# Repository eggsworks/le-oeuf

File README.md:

## Le Oeuf

An ultra-low profile (Kailh PG1425 "X Switch") keyboard inspired by Le Chiffre.

## Build guide (wired)

### BOM

- 36x 1N4148 diodes, SOD-123
- 36x Kailh PG1425 + caps
- 1x 74HC595D shift register, SOP-16
- 1x Seeed Studio XIAO RP2040

### Assembly

1. Solder all surface-mount components on the front of the board (diodes, shift register, XIAO)
2. Solder switches
3. Flash firmware, install caps, and enjoy :D

## Build guide (wireless)

Coming soon :D

## Accessories

- **["Oeuf Poché"](cases/oeuf-poche)** - A 3d-printable minimal case. Mounts with four self-tapping M2x4mm screws.
- **["SK-1425"](cases/SK-1425)** - A two-part case by [seirin-blu](https://github.com/seirin-blu).

## Firmware

ZMK firmware available from [eggsworks/zmk-config](https://github.com/eggsworks/zmk-config/)

## Production files

Gerbers, BOM, and centroid files have been added under [le-oeuf/production/](le-oeuf/production/). These Gerbers are optimized for production by PCBWay and may not necessarily be accepted by other manufacturers. The BOM and centroid file include only the diodes and the shift register, leaving the switches and MCU to be hand-soldered.

## License

This design is available under the terms of the [CERN-OHL-S](LICENSE).

## Acknowledgements

- MCU footprint derived from [ebastler/marbastlib](https://github.com/ebastler/marbastlib/)
- Switch footprint derived from [kicad-footprint-kailh-pg1425-x-switch](https://github.com/shikamiya/kicad-footprint-kailh-pg1425-x-switch)
- Layout derived from ergogen source supplied for [sporkus/le_capybara_keyboard](https://github.com/sporkus/le_capybara_keyboard)
- PCB art kindly provided by transthropology

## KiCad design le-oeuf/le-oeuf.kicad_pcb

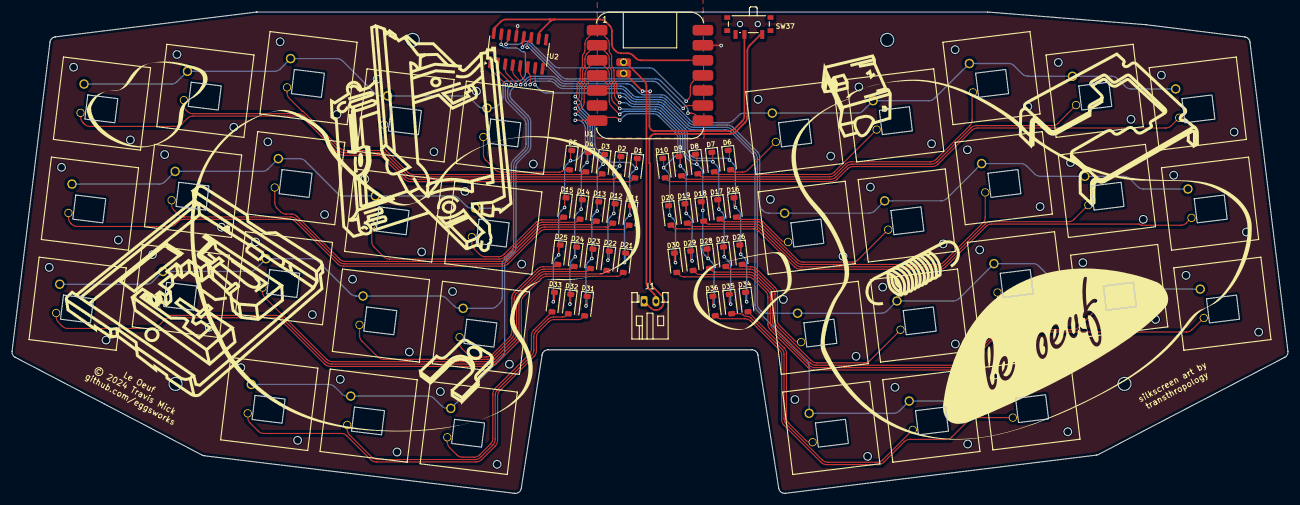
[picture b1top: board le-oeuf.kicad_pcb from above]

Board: 2 copper layers, 215.1 x 81.1 mm, 76 parts (0 on the bottom side), 57 nets.

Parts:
D1, D2, D3, D4, D5, D6, D7, D8, D9, D10, D11, D12, D13, D14, D15, D16, D17, D18, D19, D20, D21, D22, D23, D24, D25, D26, D27, D28, D29, D30, D31, D32, D33, D34, D35, D36: 1N4148W; D_SOD-123
J1: S2B-PH-K-S; JST_PH_S2B-PH-K_1x02_P2.00mm_Horizontal
SW1, SW2, SW3, SW4, SW5, SW6, SW7, SW8, SW9, SW10, SW11, SW12, SW13, SW14, SW15, SW16, SW17, SW18, SW19, SW20, SW21, SW22, SW23, SW24, SW25, SW26, SW27, SW28, SW29, SW30, SW31, SW32, SW33, SW34, SW35, SW36: PG1425; Kailh-PG1425-X-Switch
SW37: PCM12SMTR; SW_SPDT_PCM12
U1: Seeeduino Xiao nRF52840; Xiao_nRF52840_AC_Reflow
U2: 74HC595D,118; SOIC-16_3.9x9.9mm_P1.27mm

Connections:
C1: D1.1 (K), D6.1 (K), D11.1 (K), D16.1 (K), D21.1 (K), D26.1 (K), D34.1 (K), U1.1 (P0.02)
C2: D2.1 (K), D7.1 (K), D12.1 (K), D17.1 (K), D22.1 (K), D27.1 (K), D35.1 (K), U1.2 (P0.03)
C3: D3.1 (K), D8.1 (K), D13.1 (K), D18.1 (K), D23.1 (K), D28.1 (K), D31.1 (K), D36.1 (K), U1.3 (P0.28)
C4: D4.1 (K), D9.1 (K), D14.1 (K), D19.1 (K), D24.1 (K), D29.1 (K), D32.1 (K), U1.4 (P0.29)
C5: D5.1 (K), D10.1 (K), D15.1 (K), D20.1 (K), D25.1 (K), D30.1 (K), D33.1 (K), U1.7 (P1.11)
CS: U1.14 (P1.12), U2.12 (RCLK)
GND: U1.9 (GND), U2.8 (GND), U2.13 (~OE)
MOSI: U1.11 (P1.15), U2.14 (SER)
unnamed: D1.2 (A), SW1.2
unnamed: D2.2 (A), SW2.2
unnamed: D3.2 (A), SW3.2
unnamed: D4.2 (A), SW4.2
unnamed: D5.2 (A), SW5.2
unnamed: D6.2 (A), SW6.2
unnamed: D7.2 (A), SW7.2
unnamed: D8.2 (A), SW8.2
unnamed: D9.2 (A), SW9.2
unnamed: D10.2 (A), SW10.2
unnamed: D11.2 (A), SW11.2
unnamed: D12.2 (A), SW12.2
unnamed: D13.2 (A), SW13.2
unnamed: D14.2 (A), SW14.2
unnamed: D15.2 (A), SW15.2
unnamed: D16.2 (A), SW16.2
unnamed: D17.2 (A), SW17.2
unnamed: D18.2 (A), SW18.2
unnamed: D19.2 (A), SW19.2
unnamed: D20.2 (A), SW20.2
unnamed: D21.2 (A), SW21.2
unnamed: D22.2 (A), SW22.2
unnamed: D23.2 (A), SW23.2
unnamed: D24.2 (A), SW24.2
unnamed: D25.2 (A), SW25.2
unnamed: D26.2 (A), SW26.2
unnamed: D27.2 (A), SW27.2
unnamed: D28.2 (A), SW28.2
unnamed: D29.2 (A), SW29.2
unnamed: D30.2 (A), SW30.2
unnamed: D31.2 (A), SW31.2
unnamed: D32.2 (A), SW32.2
unnamed: D33.2 (A), SW33.2
unnamed: D34.2 (A), SW34.2
unnamed: D35.2 (A), SW35.2
unnamed: D36.2 (A), SW36.2
unnamed: J1.1, SW37.1 (A)
unnamed: J1.2, U1.15 (BAT-)
unnamed: SW37.2 (B), U1.16 (BAT+)
R1: SW1.1, SW2.1, SW3.1, SW4.1, SW5.1, U2.15 (QA)
R2: SW11.1, SW12.1, SW13.1, SW14.1, SW15.1, U2.1 (QB)
R3: SW21.1, SW22.1, SW23.1, SW24.1, SW25.1, U2.2 (QC)
R4: SW31.1, SW32.1, SW33.1, U2.3 (QD)
R5: SW6.1, SW7.1, SW8.1, SW9.1, SW10.1, U2.4 (QE)
R6: SW16.1, SW17.1, SW18.1, SW19.1, SW20.1, U2.5 (QF)
R7: SW26.1, SW27.1, SW28.1, SW29.1, SW30.1, U2.6 (QG)
R8: SW34.1, SW35.1, SW36.1, U2.7 (QH)
SCK: U1.13 (P1.13), U2.11 (SRCLK)
VCC: U1.10 (3V3), U2.10 (~SRCLR), U2.16 (VCC)

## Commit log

2024-11-23 Add case and update readme
2024-12-07 fix case error
2024-12-21 add step file for case
2025-02-27 Add Sei's case
2025-03-01 Add production files
2025-04-04 add bord de l'oeuf case
2025-04-07 added through hole to battery pads for easier hand soldering

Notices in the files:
le-oeuf/le-oeuf.kicad_pcb:
© 2024 Travis Mick
